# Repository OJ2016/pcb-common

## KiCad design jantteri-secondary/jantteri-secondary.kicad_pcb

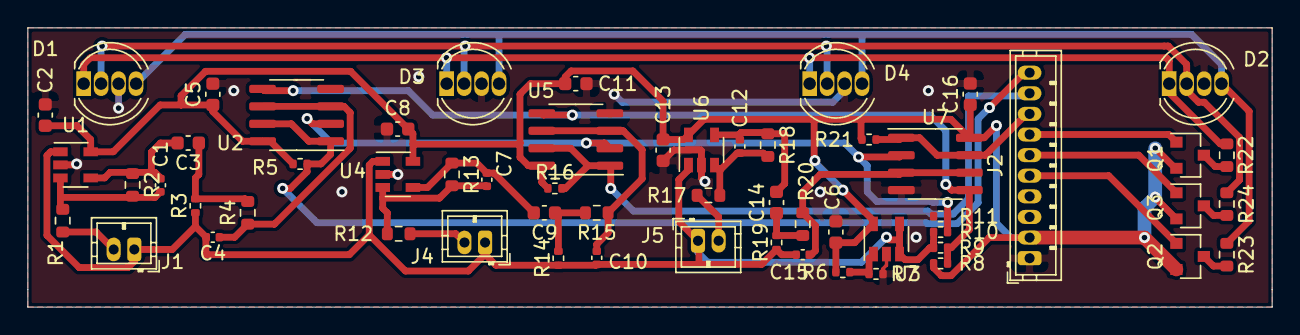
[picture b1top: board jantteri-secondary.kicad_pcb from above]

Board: 2 copper layers, 90.6 x 20.3 mm, 58 parts (0 on the bottom side), 33 nets.

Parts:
C1, C7, C12: 1n; C_0402_1005Metric
C2, C3, C5, C6, C8, C9, C11, C13, C14, C16: 10n; C_0603_1608Metric
C4, C10, C15: 22n; C_0402_1005Metric
D1, D2, D3, D4: LED_BGCR; LED_D5.0mm-4_RGB
J1, J4, J5: Conn_01x02_Male; JST_ZH_B2B-ZR_1x02_P1.50mm_Vertical
J2: Conn_01x10_Male; JST_ZH_B10B-ZR_1x10_P1.50mm_Vertical
Q1, Q2, Q3: BC808; SOT-23
R1, R12, R17: 27; R_0603_1608Metric
R2, R13, R18: 2M; R_0603_1608Metric
R3, R5, R14, R16, R19, R21: 12K; R_0402_1005Metric
R4, R15, R20: 270; R_0603_1608Metric
R6, R7: 20K; R_0402_1005Metric
R8, R11: 150K; R_0402_1005Metric
R9, R10: 3.83K; R_0402_1005Metric
R22, R23, R24: 10; R_0603_1608Metric
U1, U3, U4, U6: LMV321; SOT-23-5
U2, U5, U7: LM393; SOIC-8_3.9x4.9mm_P1.27mm

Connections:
+3V3: C2.1, C5.1, C6.1, C8.1, C11.1, C13.1, C16.1, J2.2, Q1.2, Q2.2, Q3.2, R5.1, R6.1, R8.1, R16.1, R21.1, U1.5, U2.8, U3.5, U4.5, U5.8, U6.5, U7.8
/VGND: C4.2, C10.2, C15.2, J1.1, J4.1, J5.1, R3.1, R9.2, R10.1, R14.1, R19.1, U1.1, U3.3, U3.4, U4.1, U6.1
/VGND+: R8.2, R9.1, U2.5, U5.5, U7.5
/VGND-: R10.2, R11.1, U2.2, U5.2, U7.2
/impact_sensor1/out: J2.10, R5.2, U2.1, U2.7
/impact_sensor2/out: J2.9, R16.2, U5.1, U5.7
/impact_sensor3/out: J2.8, R21.2, U7.1, U7.7
/leds/LED-B: J2.7, Q1.1
/leds/LED-G: J2.6, Q3.1
/leds/LED-R: J2.5, Q2.1
GND: C2.2, C5.2, C6.2, C8.2, C11.2, C13.2, C16.2, D1.3, D2.3, D3.3, D4.3, J2.1, R7.2, R11.2, U1.2, U2.4, U3.2, U4.2, U5.4, U6.2, U7.4
unnamed: C1.1, C3.2, R2.1, U1.4
unnamed: C1.2, R1.1, R2.2, U1.3
unnamed: C3.1, R3.2, R4.2
unnamed: C4.1, R4.1, U2.3, U2.6
unnamed: C7.1, C9.2, R13.1, U4.4
unnamed: C7.2, R12.1, R13.2, U4.3
unnamed: C9.1, R14.2, R15.2
unnamed: C10.1, R15.1, U5.3, U5.6
unnamed: C12.1, C14.2, R18.1, U6.4
unnamed: C12.2, R17.1, R18.2, U6.3
unnamed: C14.1, R19.2, R20.2
unnamed: C15.1, R20.1, U7.3, U7.6
unnamed: D1.1, D2.1, D3.1, D4.1, R22.2
unnamed: D1.2, D2.2, D3.2, D4.2, R24.1
unnamed: D1.4, D2.4, D3.4, D4.4, R23.1
unnamed: J1.2, R1.2
unnamed: J4.2, R12.2
unnamed: J5.2, R17.2
unnamed: Q1.3, R22.1
unnamed: Q2.3, R23.2
unnamed: Q3.3, R24.2
unnamed: R6.2, R7.1, U3.1
